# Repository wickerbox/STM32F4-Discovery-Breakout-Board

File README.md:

stm32f4-discovery-breakout-board
================================

The $15 STM32F4-Discovery ARM Cortex M4 development board is an amazing price but it unfortunately has columns of male pin headers that are awkwardly positioned so you can't use it directly with a standard breadboard.

This pair of breakout boards takes the male pins to female headers. If you don't mind a permanent solution, you can solder the boards directly to the male pins and save $5 in 2x25-pin female headers.

The git repo contains Eagle files and generated fab-ready gerbers for the STM32F4-DISCOVERY breakout board. The complete build log is on <a href="http://jennerhanni.net/2015/02/stm32f4-disc-breakout/">my site with more photos</a>.

You definitely want to use version 2 but I'm including version 1, even if you're routing this on a home PCB router. All traces are on the bottom side so there's no need for plated through holes if you're using the 2x25-pin female headers. Place the components on the top of the breakout boards and solder the pins on the bottom side. It'll come out just fine.

Total cost for your own set of three is $45.37.

I shared the project so you can <a href="https://oshpark.com/shared_projects/GJyFucOY">order boards for $33.95 from OSH Park</a>.

I used these Sullins female headers:  

- Qty 4 of <a href="https://www.digikey.com/product-detail/en/PPTC251LFBN-RC/S7023-ND/810163">PPTC251LFBN-RC</a> 1×25 0.1" for $1.41 each
- Qty 2 of <a href="https://www.digikey.com/product-detail/en/SFH11-PBPC-D25-ST-BK/S9201-ND/1990094">SFH11-PBPC-D25-ST-BK</a> 2×25 0.1" for $2.89 each.

The project is released under the <a href="http://www.ohwr.org/attachments/2388/cern_ohl_v_1_2.txt">CERN Open Hardware License v1.2</a>.

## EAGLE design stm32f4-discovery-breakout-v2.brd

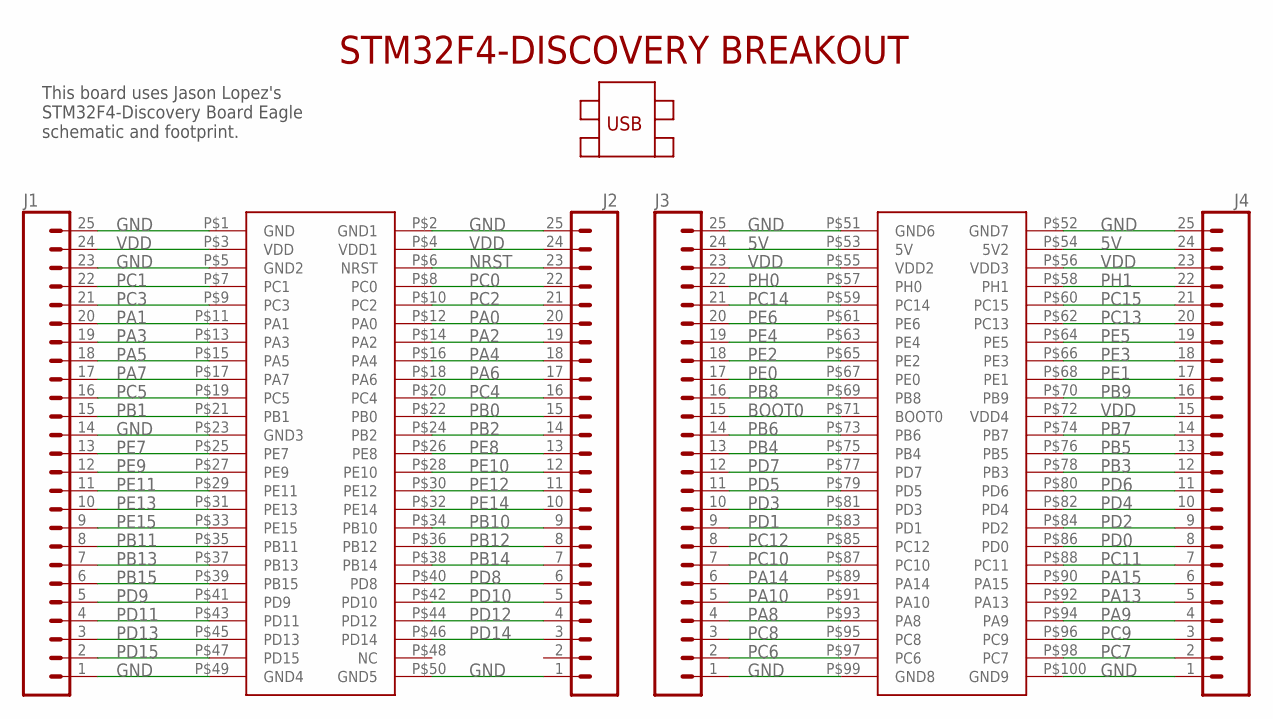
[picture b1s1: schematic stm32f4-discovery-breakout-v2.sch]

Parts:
J1, J2, J3, J4: M25LOCK_LONGPADS; 1X25_LOCK_LONGPADS
U$1: STM32F4-DISCOVERY

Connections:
5V: J3.24, J4.24, U$1.P$53 (5V), U$1.P$54 (5V2)
BOOT0: J3.15, U$1.P$71 (BOOT0)
GND: J1.1, J1.14, J1.23, J1.25, J2.1, J2.25, J3.1, J3.25, J4.1, J4.25, U$1.P$1 (GND), U$1.P$2 (GND1), U$1.P$5 (GND2), U$1.P$23 (GND3), U$1.P$49 (GND4), U$1.P$50 (GND5), U$1.P$51 (GND6), U$1.P$52 (GND7), U$1.P$99 (GND8), U$1.P$100 (GND9)
NRST: J2.23, U$1.P$6 (NRST)
PA0: J2.20, U$1.P$12 (PA0)
PA1: J1.20, U$1.P$11 (PA1)
PA2: J2.19, U$1.P$14 (PA2)
PA3: J1.19, U$1.P$13 (PA3)
PA4: J2.18, U$1.P$16 (PA4)
PA5: J1.18, U$1.P$15 (PA5)
PA6: J2.17, U$1.P$18 (PA6)
PA7: J1.17, U$1.P$17 (PA7)
PA8: J3.4, U$1.P$93 (PA8)
PA9: J4.4, U$1.P$94 (PA9)
PA10: J3.5, U$1.P$91 (PA10)
PA13: J4.5, U$1.P$92 (PA13)
PA14: J3.6, U$1.P$89 (PA14)
PA15: J4.6, U$1.P$90 (PA15)
PB0: J2.15, U$1.P$22 (PB0)
PB1: J1.15, U$1.P$21 (PB1)
PB2: J2.14, U$1.P$24 (PB2)
PB3: J4.12, U$1.P$78 (PB3)
PB4: J3.13, U$1.P$75 (PB4)
PB5: J4.13, U$1.P$76 (PB5)
PB6: J3.14, U$1.P$73 (PB6)
PB7: J4.14, U$1.P$74 (PB7)
PB8: J3.16, U$1.P$69 (PB8)
PB9: J4.16, U$1.P$70 (PB9)
PB10: J2.9, U$1.P$34 (PB10)
PB11: J1.8, U$1.P$35 (PB11)
PB12: J2.8, U$1.P$36 (PB12)
PB13: J1.7, U$1.P$37 (PB13)
PB14: J2.7, U$1.P$38 (PB14)
PB15: J1.6, U$1.P$39 (PB15)
PC0: J2.22, U$1.P$8 (PC0)
PC1: J1.22, U$1.P$7 (PC1)
PC2: J2.21, U$1.P$10 (PC2)
PC3: J1.21, U$1.P$9 (PC3)
PC4: J2.16, U$1.P$20 (PC4)
PC5: J1.16, U$1.P$19 (PC5)
PC6: J3.2, U$1.P$97 (PC6)
PC7: J4.2, U$1.P$98 (PC7)
PC8: J3.3, U$1.P$95 (PC8)
PC9: J4.3, U$1.P$96 (PC9)
PC10: J3.7, U$1.P$87 (PC10)
PC11: J4.7, U$1.P$88 (PC11)
PC12: J3.8, U$1.P$85 (PC12)
PC13: J4.20, U$1.P$62 (PC13)
PC14: J3.21, U$1.P$59 (PC14)
PC15: J4.21, U$1.P$60 (PC15)
PD0: J4.8, U$1.P$86 (PD0)
PD1: J3.9, U$1.P$83 (PD1)
PD2: J4.9, U$1.P$84 (PD2)
PD3: J3.10, U$1.P$81 (PD3)
PD4: J4.10, U$1.P$82 (PD4)
PD5: J3.11, U$1.P$79 (PD5)
PD6: J4.11, U$1.P$80 (PD6)
PD7: J3.12, U$1.P$77 (PD7)
PD8: J2.6, U$1.P$40 (PD8)
PD9: J1.5, U$1.P$41 (PD9)
PD10: J2.5, U$1.P$42 (PD10)
PD11: J1.4, U$1.P$43 (PD11)
PD12: J2.4, U$1.P$44 (PD12)
PD13: J1.3, U$1.P$45 (PD13)
PD14: J2.3, U$1.P$46 (PD14)
PD15: J1.2, U$1.P$47 (PD15)
PE0: J3.17, U$1.P$67 (PE0)
PE1: J4.17, U$1.P$68 (PE1)
PE2: J3.18, U$1.P$65 (PE2)
PE3: J4.18, U$1.P$66 (PE3)
PE4: J3.19, U$1.P$63 (PE4)
PE5: J4.19, U$1.P$64 (PE5)
PE6: J3.20, U$1.P$61 (PE6)
PE7: J1.13, U$1.P$25 (PE7)
PE8: J2.13, U$1.P$26 (PE8)
PE9: J1.12, U$1.P$27 (PE9)
PE10: J2.12, U$1.P$28 (PE10)
PE11: J1.11, U$1.P$29 (PE11)
PE12: J2.11, U$1.P$30 (PE12)
PE13: J1.10, U$1.P$31 (PE13)
PE14: J2.10, U$1.P$32 (PE14)
PE15: J1.9, U$1.P$33 (PE15)
PH0: J3.22, U$1.P$57 (PH0)
PH1: J4.22, U$1.P$58 (PH1)
VDD: J1.24, J2.24, J3.23, J4.15, J4.23, U$1.P$3 (VDD), U$1.P$4 (VDD1), U$1.P$55 (VDD2), U$1.P$56 (VDD3), U$1.P$72 (VDD4)

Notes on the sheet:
This board uses Jason Lopez's STM32F4-Discovery Board Eagle schematic and footprint.

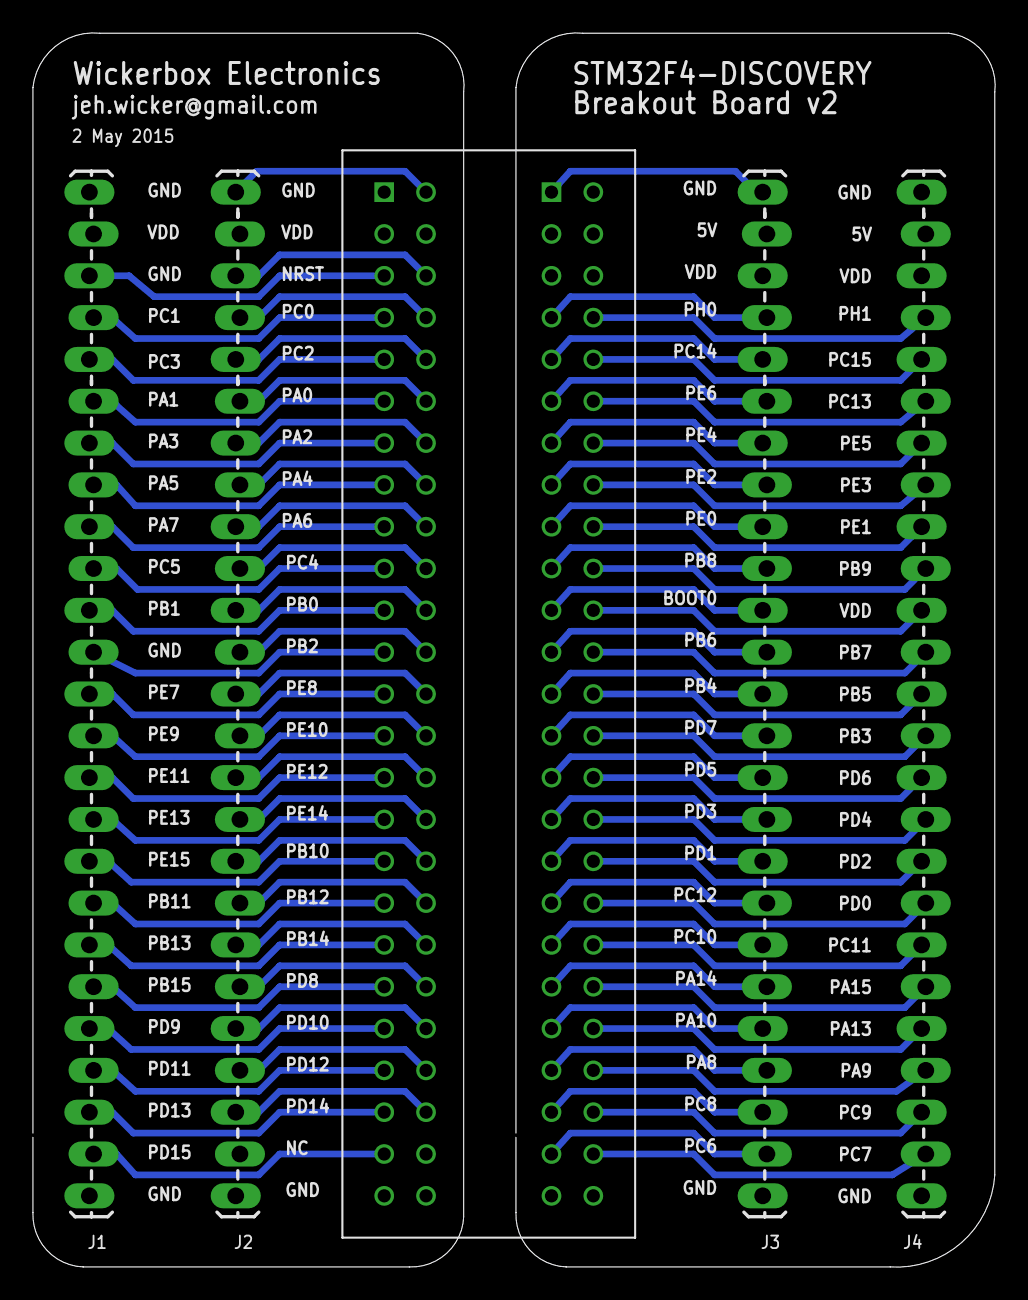
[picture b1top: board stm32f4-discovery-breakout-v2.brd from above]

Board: 2 copper layers, 58.4 x 75.0 mm, 5 parts (0 on the bottom side), 85 nets.

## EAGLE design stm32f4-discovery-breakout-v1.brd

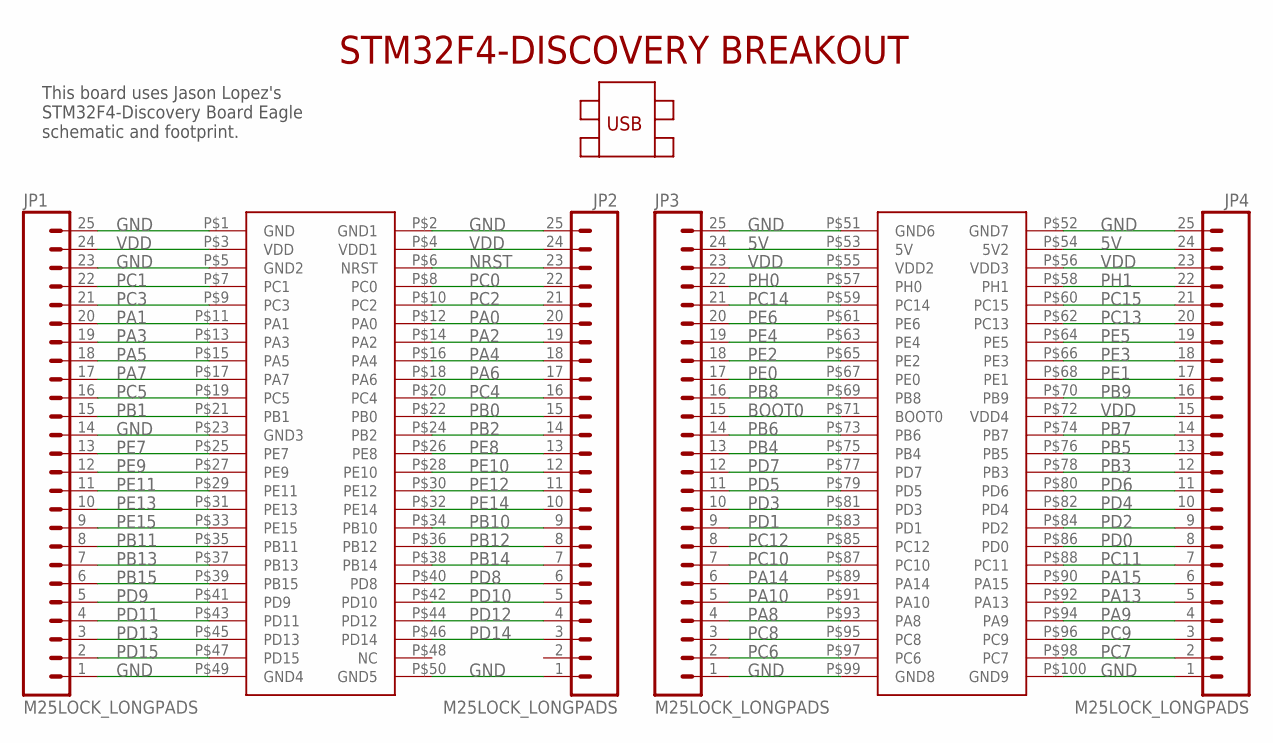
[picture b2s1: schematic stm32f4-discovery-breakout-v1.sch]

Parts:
JP1, JP2, JP3, JP4: M25LOCK_LONGPADS; 1X25_LOCK_LONGPADS
U$1: STM32F4-DISCOVERY

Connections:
5V: JP3.24, JP4.24, U$1.P$53 (5V), U$1.P$54 (5V2)
BOOT0: JP3.15, U$1.P$71 (BOOT0)
GND: JP1.1, JP1.14, JP1.23, JP1.25, JP2.1, JP2.25, JP3.1, JP3.25, JP4.1, JP4.25, U$1.P$1 (GND), U$1.P$2 (GND1), U$1.P$5 (GND2), U$1.P$23 (GND3), U$1.P$49 (GND4), U$1.P$50 (GND5), U$1.P$51 (GND6), U$1.P$52 (GND7), U$1.P$99 (GND8), U$1.P$100 (GND9)
NRST: JP2.23, U$1.P$6 (NRST)
PA0: JP2.20, U$1.P$12 (PA0)
PA1: JP1.20, U$1.P$11 (PA1)
PA2: JP2.19, U$1.P$14 (PA2)
PA3: JP1.19, U$1.P$13 (PA3)
PA4: JP2.18, U$1.P$16 (PA4)
PA5: JP1.18, U$1.P$15 (PA5)
PA6: JP2.17, U$1.P$18 (PA6)
PA7: JP1.17, U$1.P$17 (PA7)
PA8: JP3.4, U$1.P$93 (PA8)
PA9: JP4.4, U$1.P$94 (PA9)
PA10: JP3.5, U$1.P$91 (PA10)
PA13: JP4.5, U$1.P$92 (PA13)
PA14: JP3.6, U$1.P$89 (PA14)
PA15: JP4.6, U$1.P$90 (PA15)
PB0: JP2.15, U$1.P$22 (PB0)
PB1: JP1.15, U$1.P$21 (PB1)
PB2: JP2.14, U$1.P$24 (PB2)
PB3: JP4.12, U$1.P$78 (PB3)
PB4: JP3.13, U$1.P$75 (PB4)
PB5: JP4.13, U$1.P$76 (PB5)
PB6: JP3.14, U$1.P$73 (PB6)
PB7: JP4.14, U$1.P$74 (PB7)
PB8: JP3.16, U$1.P$69 (PB8)
PB9: JP4.16, U$1.P$70 (PB9)
PB10: JP2.9, U$1.P$34 (PB10)
PB11: JP1.8, U$1.P$35 (PB11)
PB12: JP2.8, U$1.P$36 (PB12)
PB13: JP1.7, U$1.P$37 (PB13)
PB14: JP2.7, U$1.P$38 (PB14)
PB15: JP1.6, U$1.P$39 (PB15)
PC0: JP2.22, U$1.P$8 (PC0)
PC1: JP1.22, U$1.P$7 (PC1)
PC2: JP2.21, U$1.P$10 (PC2)
PC3: JP1.21, U$1.P$9 (PC3)
PC4: JP2.16, U$1.P$20 (PC4)
PC5: JP1.16, U$1.P$19 (PC5)
PC6: JP3.2, U$1.P$97 (PC6)
PC7: JP4.2, U$1.P$98 (PC7)
PC8: JP3.3, U$1.P$95 (PC8)
PC9: JP4.3, U$1.P$96 (PC9)
PC10: JP3.7, U$1.P$87 (PC10)
PC11: JP4.7, U$1.P$88 (PC11)
PC12: JP3.8, U$1.P$85 (PC12)
PC13: JP4.20, U$1.P$62 (PC13)
PC14: JP3.21, U$1.P$59 (PC14)
PC15: JP4.21, U$1.P$60 (PC15)
PD0: JP4.8, U$1.P$86 (PD0)
PD1: JP3.9, U$1.P$83 (PD1)
PD2: JP4.9, U$1.P$84 (PD2)
PD3: JP3.10, U$1.P$81 (PD3)
PD4: JP4.10, U$1.P$82 (PD4)
PD5: JP3.11, U$1.P$79 (PD5)
PD6: JP4.11, U$1.P$80 (PD6)
PD7: JP3.12, U$1.P$77 (PD7)
PD8: JP2.6, U$1.P$40 (PD8)
PD9: JP1.5, U$1.P$41 (PD9)
PD10: JP2.5, U$1.P$42 (PD10)
PD11: JP1.4, U$1.P$43 (PD11)
PD12: JP2.4, U$1.P$44 (PD12)
PD13: JP1.3, U$1.P$45 (PD13)
PD14: JP2.3, U$1.P$46 (PD14)
PD15: JP1.2, U$1.P$47 (PD15)
PE0: JP3.17, U$1.P$67 (PE0)
PE1: JP4.17, U$1.P$68 (PE1)
PE2: JP3.18, U$1.P$65 (PE2)
PE3: JP4.18, U$1.P$66 (PE3)
PE4: JP3.19, U$1.P$63 (PE4)
PE5: JP4.19, U$1.P$64 (PE5)
PE6: JP3.20, U$1.P$61 (PE6)
PE7: JP1.13, U$1.P$25 (PE7)
PE8: JP2.13, U$1.P$26 (PE8)
PE9: JP1.12, U$1.P$27 (PE9)
PE10: JP2.12, U$1.P$28 (PE10)
PE11: JP1.11, U$1.P$29 (PE11)
PE12: JP2.11, U$1.P$30 (PE12)
PE13: JP1.10, U$1.P$31 (PE13)
PE14: JP2.10, U$1.P$32 (PE14)
PE15: JP1.9, U$1.P$33 (PE15)
PH0: JP3.22, U$1.P$57 (PH0)
PH1: JP4.22, U$1.P$58 (PH1)
VDD: JP1.24, JP2.24, JP3.23, JP4.15, JP4.23, U$1.P$3 (VDD), U$1.P$4 (VDD1), U$1.P$55 (VDD2), U$1.P$56 (VDD3), U$1.P$72 (VDD4)

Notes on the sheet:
This board uses Jason Lopez's STM32F4-Discovery Board Eagle schematic and footprint.

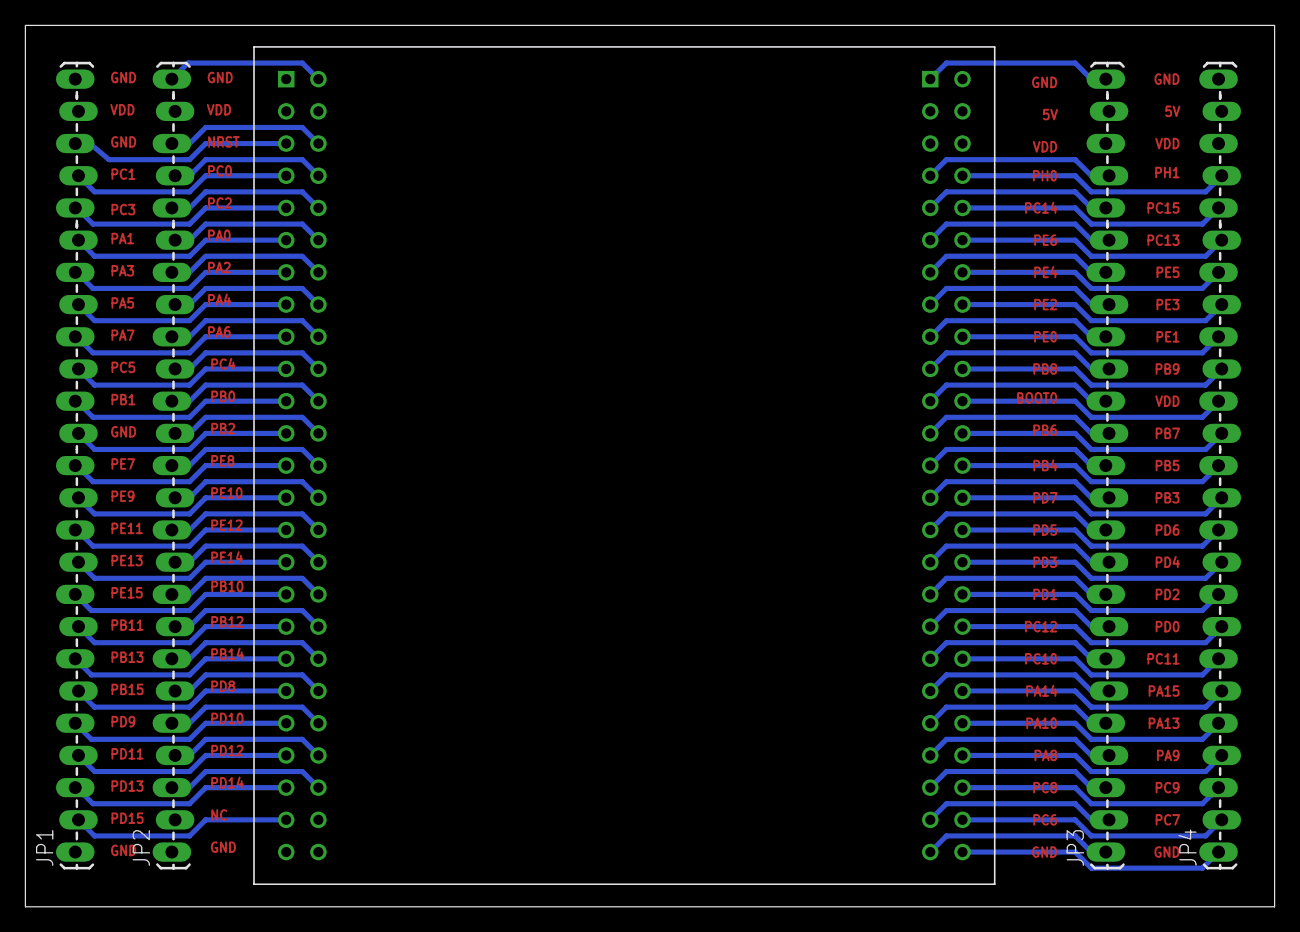
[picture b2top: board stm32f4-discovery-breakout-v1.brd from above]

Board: 2 copper layers, 98.5 x 69.5 mm, 5 parts (0 on the bottom side), 85 nets.

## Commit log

2014-05-09 Used unchecked footprint. Layout done. Ready for test.
2015-06-07 Is this the final?
2015-10-11 Fixed up version numbers.
2015-10-11 Relicensed to CERN OHL v1.2
2015-10-16 Added license note.
2015-10-16 Added v2 gerbers.

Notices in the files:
parts and their libraries:
SparkFun-Connectors: Licensing: Creative Commons ShareAlike 4.0 International - https://creativecommons.org/licenses/by-sa/4.0
